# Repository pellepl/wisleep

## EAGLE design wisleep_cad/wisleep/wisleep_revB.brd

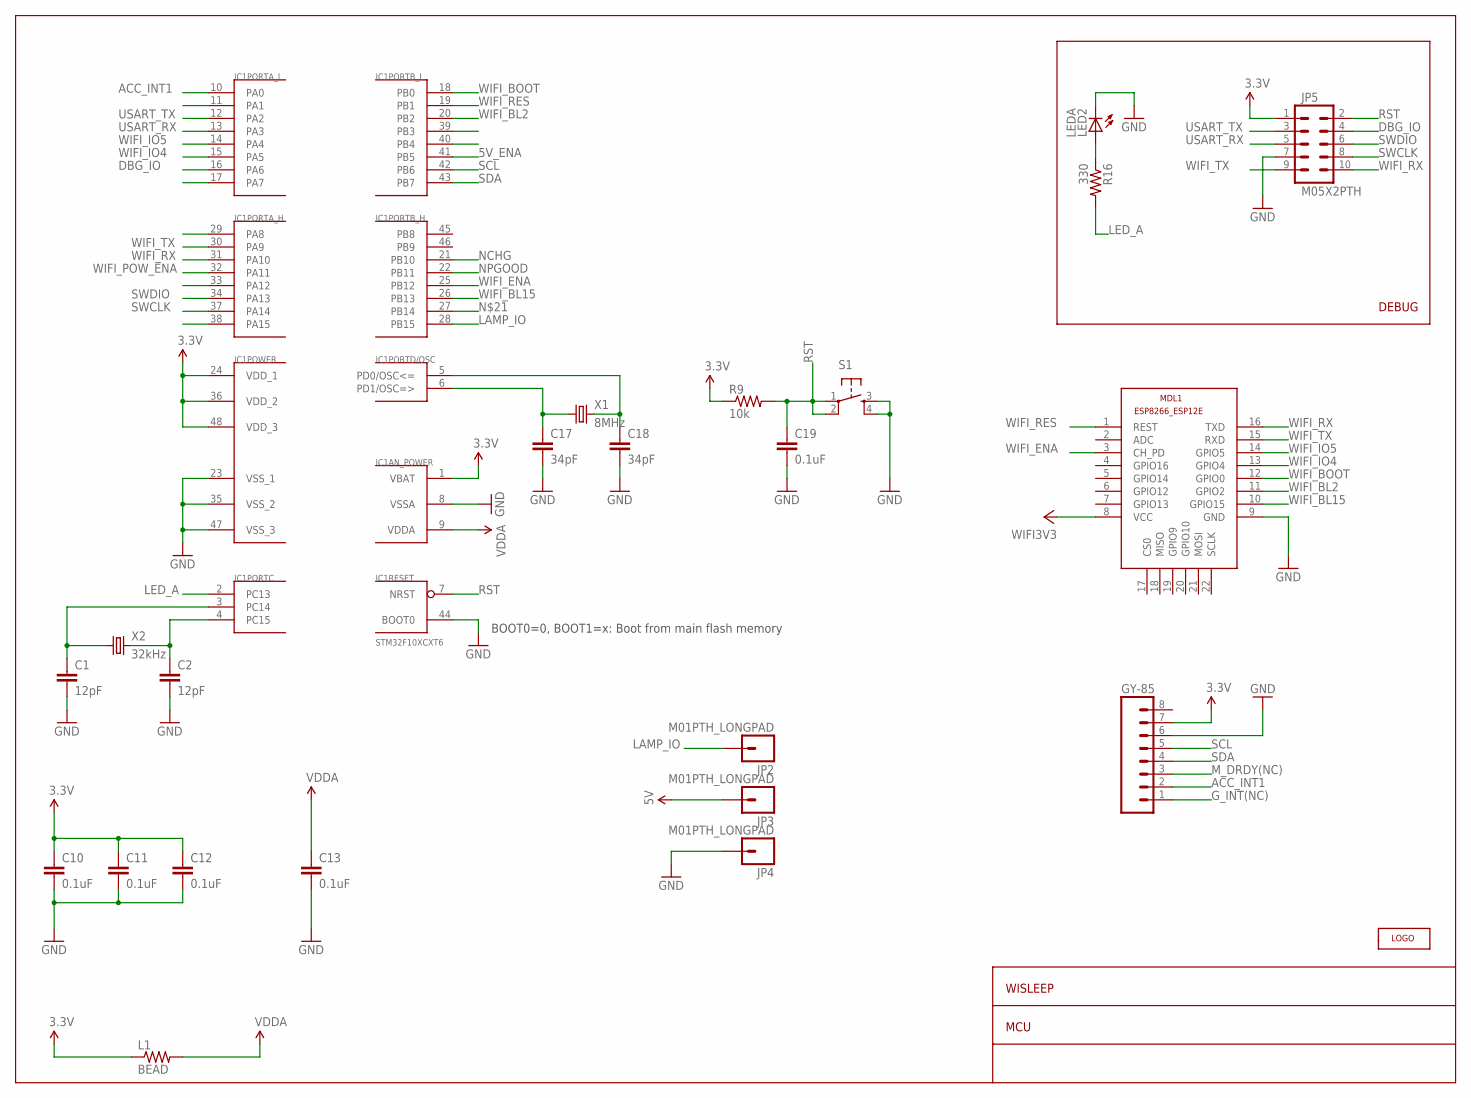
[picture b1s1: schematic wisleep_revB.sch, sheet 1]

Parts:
C1, C2: 12pF; C0402
C10, C11, C12, C13, C19: 0.1uF; C0402
C17, C18: 34pF; C0402
GY-85: M08; 1X08
IC1: STM32F10XCXT6; TQFP48
JP2, JP3, JP4: M01PTH_LONGPAD; 1X01_LONGPAD
JP5: M05X2PTH; AVR_ICSP
L1: BEAD; 0603_GEN
LED2: LEDA; LED-0603
MDL1: ESP8266-12EESP8266-ESP12E; ESP8266-ESP12E
R9: 10k; C0402
R16: 330; C0402
S1: TAC_SWITCHSMD; TACTILE_SWITCH_SMD
U$7: LOGOLOGO; LOGO
X1: 8MHz; CRYSTAL_SMD_5X3.2_7A
X2: 32kHz; CRYSTAL_SMD_2X0.6

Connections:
3.3V: C10.1, C11.1, C12.1, GY-85.7, IC1.1 (VBAT), IC1.24 (VDD_1), IC1.36 (VDD_2), IC1.48 (VDD_3), JP5.1, L1.1, R9.1; also elsewhere on the board
5V: JP3.1; also elsewhere on the board
5V_ENA: IC1.41 (PB5); also elsewhere on the board
ACC_INT1: GY-85.2, IC1.10 (PA0)
DBG_IO: IC1.16 (PA6), JP5.4
GND: C1.2, C2.2, C10.2, C11.2, C12.2, C13.2, C17.2, C18.2, C19.2, GY-85.6, IC1.8 (VSSA), IC1.23 (VSS_1), IC1.35 (VSS_2), IC1.44 (BOOT0), IC1.47 (VSS_3), JP4.1, JP5.7, LED2.C, MDL1.9 (GND), S1.3, S1.4; also elsewhere on the board
G_INT(NC): GY-85.1
LAMP_IO: IC1.28 (PB15), JP2.1
LED_A: IC1.2 (PC13), R16.2
M_DRDY(NC): GY-85.3
unnamed: C1.1, IC1.3 (PC14), X2.P$1 (1)
unnamed: C2.1, IC1.4 (PC15), X2.P$2 (2)
unnamed: LED2.A, R16.1
NCHG: IC1.21 (PB10); also elsewhere on the board
NPGOOD: IC1.22 (PB11); also elsewhere on the board
OSCI: C18.1, IC1.5 (PD0/OSC<=), X1.P$2 (2)
OSCO: C17.1, IC1.6 (PD1/OSC=>), X1.P$1 (1)
PB3: IC1.39 (PB3)
RST: C19.1, IC1.7 (NRST), JP5.2, R9.2, S1.1, S1.2
SCL: GY-85.5, IC1.42 (PB6)
SDA: GY-85.4, IC1.43 (PB7)
SWCLK: IC1.37 (PA14), JP5.8
SWDIO: IC1.34 (PA13), JP5.6
USART_RX: IC1.13 (PA3), JP5.5
USART_TX: IC1.12 (PA2), JP5.3
VCC: MDL1.8 (VCC); also elsewhere on the board
VDDA: C13.1, IC1.9 (VDDA), L1.2
WIFI_BL2: IC1.20 (PB2), MDL1.11 (GPIO2)
WIFI_BL15: IC1.26 (PB13), MDL1.10 (GPIO15)
WIFI_BOOT: IC1.18 (PB0), MDL1.12 (GPIO0)
WIFI_ENA: IC1.25 (PB12), MDL1.3 (CH_PD)
WIFI_IO4: IC1.15 (PA5), MDL1.13 (GPIO4)
WIFI_IO5: IC1.14 (PA4), MDL1.14 (GPIO5)
WIFI_POW_ENA: IC1.32 (PA11); also elsewhere on the board
WIFI_RES: IC1.19 (PB1), MDL1.1 (REST)
WIFI_RX: IC1.31 (PA10), JP5.10, MDL1.16 (TXD)
WIFI_TX: IC1.30 (PA9), JP5.9, MDL1.15 (RXD)

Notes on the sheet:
WISLEEP
MCU
DEBUG
BOOT0=0, BOOT1=x: Boot from main flash memory

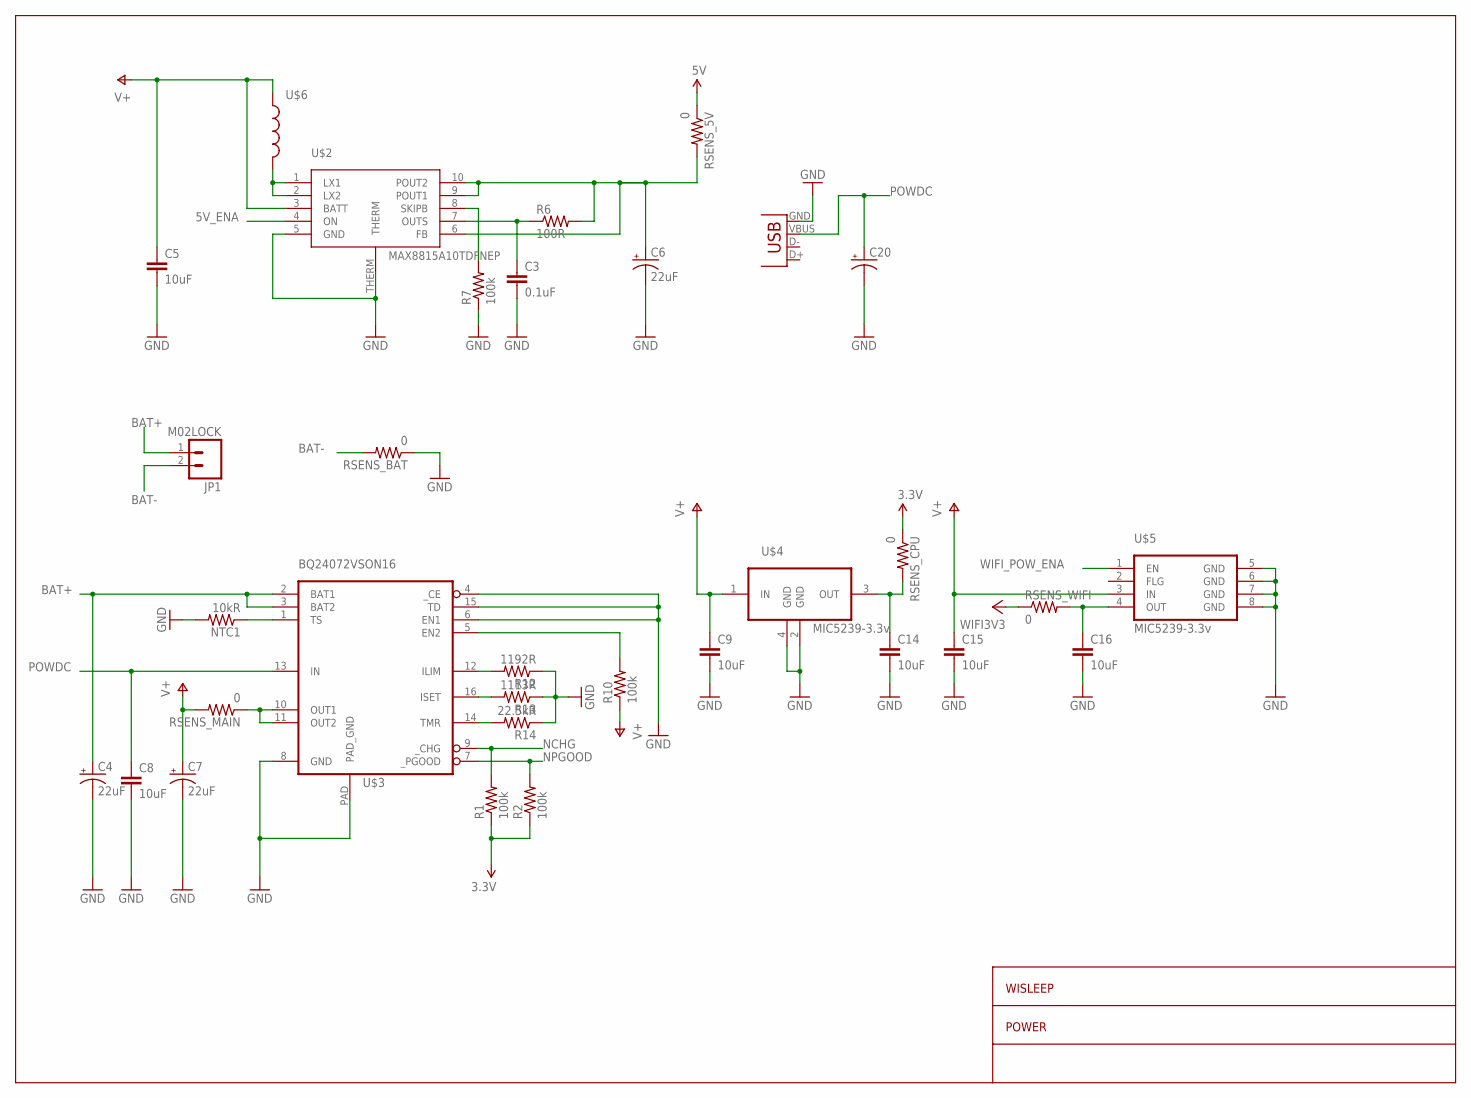
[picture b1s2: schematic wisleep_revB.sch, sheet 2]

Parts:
C3: 0.1uF; C0402
C4, C6, C7: 22uF; EIA3216
C5, C8, C9, C14, C15, C16: 10uF; C0402
C20: CAP_POL6032; EIA6032
JP1: M02LOCK; 1X02_LOCK
NTC1: 10kR; C0402
R1, R2, R7, R10: 100k; C0402
R6: 100R; C0402
R12: 1192R; C0402
R13: 1113R; C0402
R14: 22.5kR; C0402
RSENS_5V: 0; C0402
RSENS_BAT: 0; C0402
RSENS_CPU: 0; C0402
RSENS_MAIN: 0; C0402
RSENS_WIFI: 0; C0402
U$2: MAX8815A10TDFNEP; 10-TDFN-EP
U$3: BQ24072VSON16; VSON16
U$4: MIC5239-3.3v; SOT223
U$5: MIC5239-3.3v; MSOP08
U$6: INDUCTOR3014; INDUCTOR-3014
X3: USB-MINIB

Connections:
3.3V: R1.1, R2.1, RSENS_CPU.1; also elsewhere on the board
5V: RSENS_5V.1; also elsewhere on the board
5V_ENA: U$2.4 (ON); also elsewhere on the board
BAT+: C4.A (+), JP1.1, U$3.2 (BAT1), U$3.3 (BAT2)
BAT-: JP1.2, RSENS_BAT.2
GND: C3.2, C4.C (-), C5.2, C6.C (-), C7.C (-), C8.2, C9.2, C14.2, C15.2, C16.2, C20.P$2 (-), NTC1.2, R7.1, R12.1, R13.1, R14.1, RSENS_BAT.1, U$2.5 (GND), U$2.THERM, U$3.4 (_CE), U$3.6 (EN1), U$3.8 (GND), U$3.15 (TD), U$3.PAD (PAD_GND), U$4.2 (GND), U$4.4 (GND), U$5.5 (GND), U$5.6 (GND), U$5.7 (GND), U$5.8 (GND), X3.GND; also elsewhere on the board
unnamed: C6.A (+), R6.2, RSENS_5V.2, U$2.6 (FB), U$2.9 (POUT1), U$2.10 (POUT2)
unnamed: RSENS_MAIN.1, U$3.10 (OUT1), U$3.11 (OUT2)
unnamed: R14.2, U$3.14 (TMR)
unnamed: NTC1.1, U$3.1 (TS)
unnamed: R10.2, U$3.5 (EN2)
unnamed: R12.2, U$3.12 (ILIM)
unnamed: R13.2, U$3.16 (ISET)
unnamed: C14.1, RSENS_CPU.2, U$4.3 (OUT)
unnamed: C16.1, RSENS_WIFI.2, U$5.4 (OUT)
unnamed: U$2.1 (LX1), U$2.2 (LX2), U$6.P$2 (2)
unnamed: C3.1, R6.1, U$2.7 (OUTS)
unnamed: R7.2, U$2.8 (SKIPB)
NCHG: R1.2, U$3.9 (_CHG); also elsewhere on the board
NPGOOD: R2.2, U$3.7 (_PGOOD); also elsewhere on the board
POWDC: C8.1, C20.P$1 (+), U$3.13 (IN), X3.VBUS
V+: C5.1, C7.A (+), C9.1, C15.1, R10.1, RSENS_MAIN.2, U$2.3 (BATT), U$4.1 (IN), U$5.3 (IN), U$6.P$1 (1)
VCC: RSENS_WIFI.1; also elsewhere on the board
WIFI_POW_ENA: U$5.1 (EN); also elsewhere on the board

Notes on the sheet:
WISLEEP
POWER

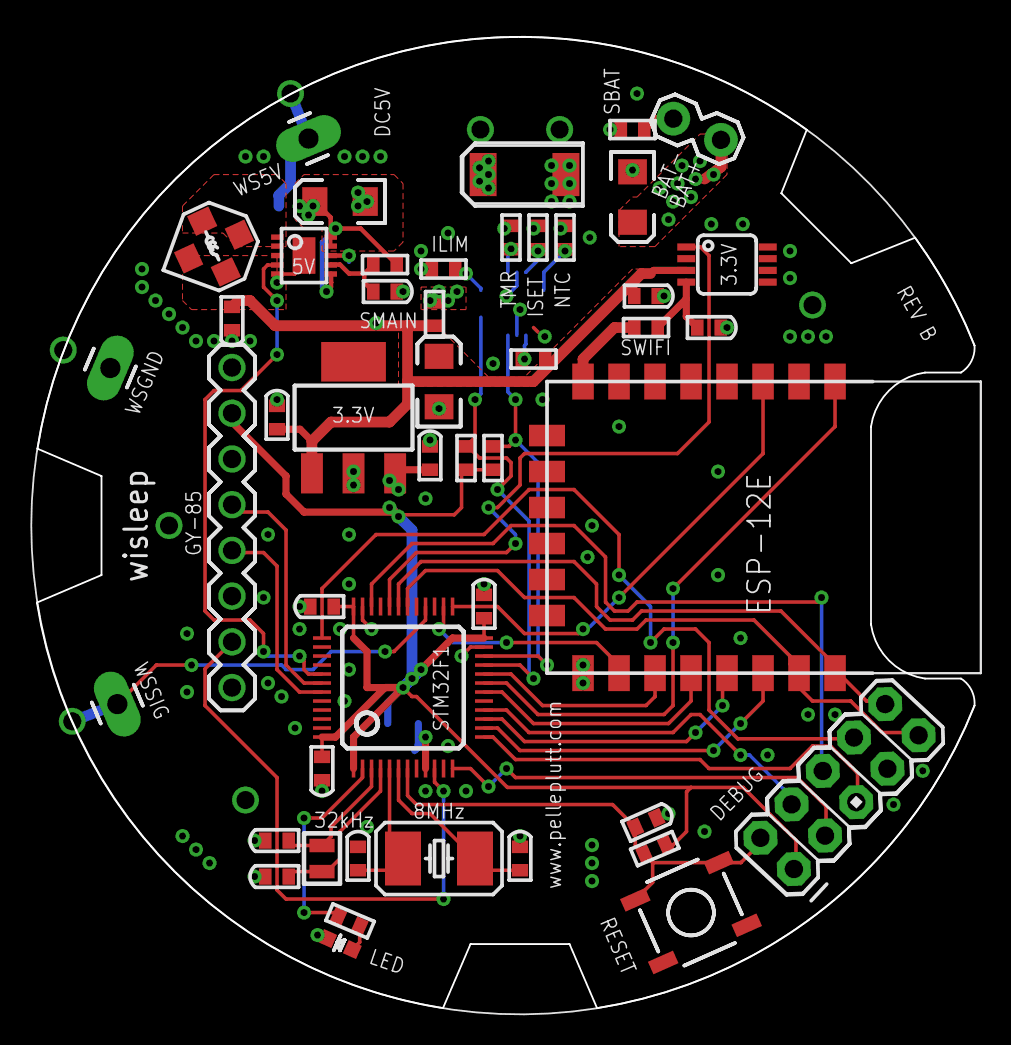
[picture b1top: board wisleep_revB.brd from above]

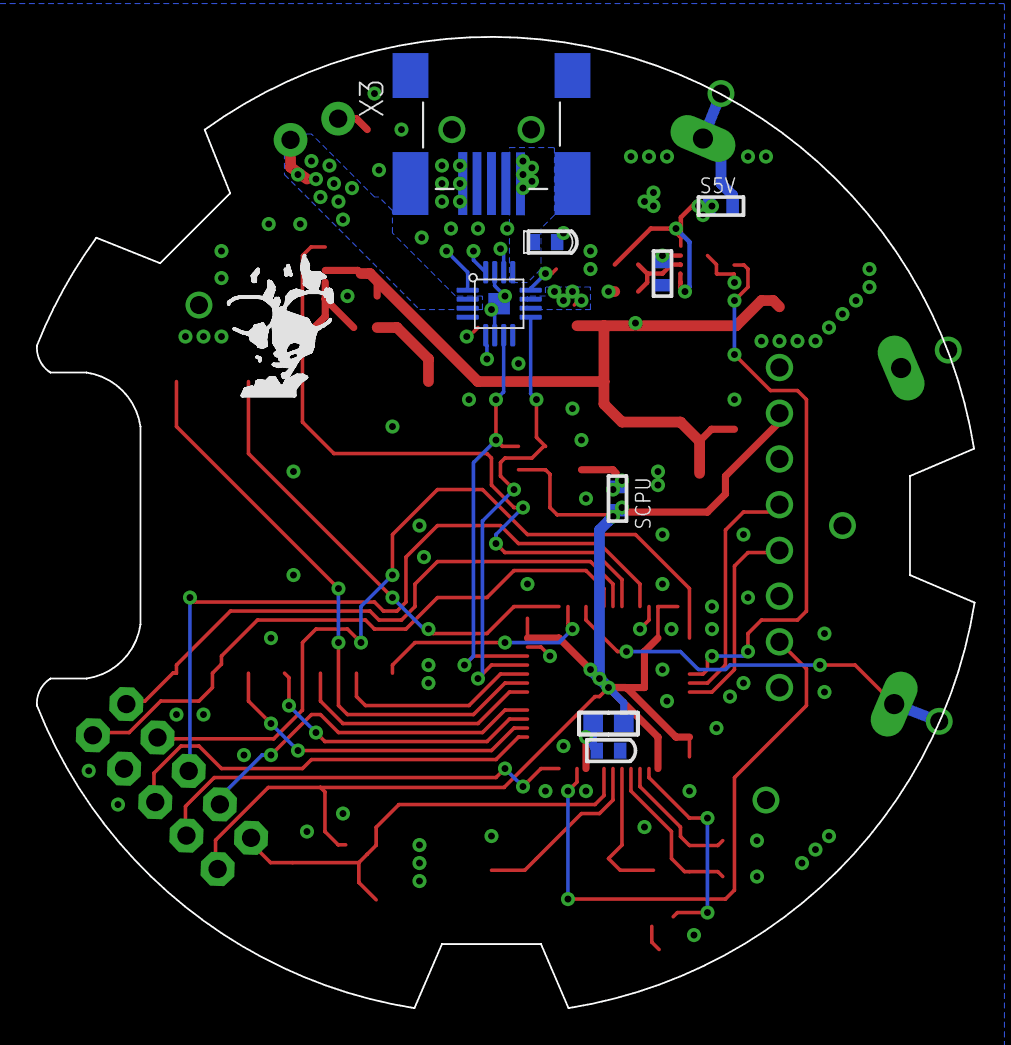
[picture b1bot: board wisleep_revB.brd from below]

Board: 2 copper layers, 52.1 x 54.0 mm, 56 parts (9 on the bottom side), 50 nets.

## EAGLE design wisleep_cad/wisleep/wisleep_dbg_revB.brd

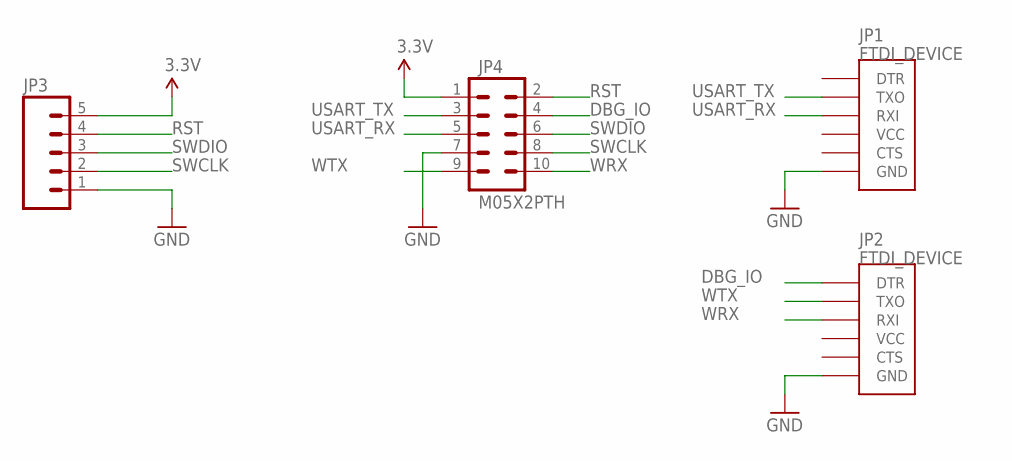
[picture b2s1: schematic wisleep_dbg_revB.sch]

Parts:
JP1, JP2: FTDI_DEVICE; FTDI_DEVICE_SIDE
JP3: M05LOCK; 1X05_LOCK
JP4: M05X2PTH; AVR_ICSP

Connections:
3.3V: JP3.5, JP4.1
DBG_IO: JP2.P$1 (DTR), JP4.4
GND: JP1.P$6 (GND), JP2.P$6 (GND), JP3.1, JP4.7
RST: JP3.4, JP4.2
SWCLK: JP3.2, JP4.8
SWDIO: JP3.3, JP4.6
USART_RX: JP1.P$3 (RXI), JP4.5
USART_TX: JP1.P$2 (TXO), JP4.3
WRX: JP2.P$3 (RXI), JP4.10
WTX: JP2.P$2 (TXO), JP4.9

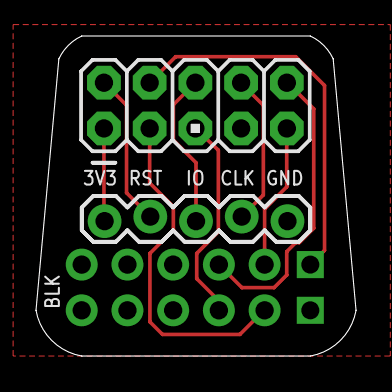
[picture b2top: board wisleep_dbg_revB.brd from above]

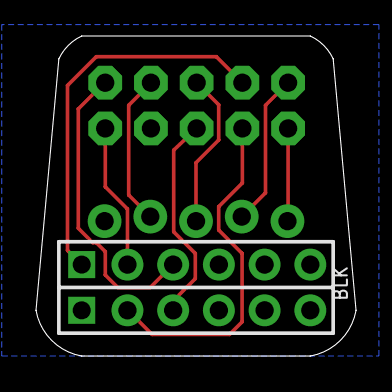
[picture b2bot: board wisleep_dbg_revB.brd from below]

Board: 2 copper layers, 17.8 x 17.8 mm, 4 parts (2 on the bottom side), 10 nets.

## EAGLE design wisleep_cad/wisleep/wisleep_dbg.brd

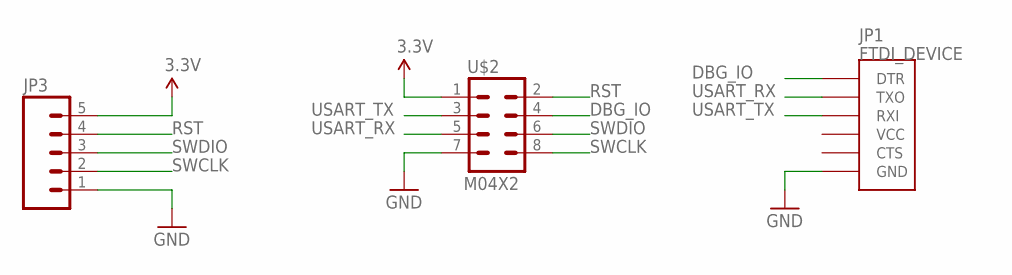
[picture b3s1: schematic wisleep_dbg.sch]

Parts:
JP1: FTDI_DEVICE; FTDI_DEVICE_SIDE
JP3: M05LOCK; 1X05_LOCK
U$2: M04X2; 2X4

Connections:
3.3V: JP3.5, U$2.1
DBG_IO: JP1.P$1 (DTR), U$2.4
GND: JP1.P$6 (GND), JP3.1, U$2.7
RST: JP3.4, U$2.2
SWCLK: JP3.2, U$2.8
SWDIO: JP3.3, U$2.6
USART_RX: JP1.P$2 (TXO), U$2.5
USART_TX: JP1.P$3 (RXI), U$2.3

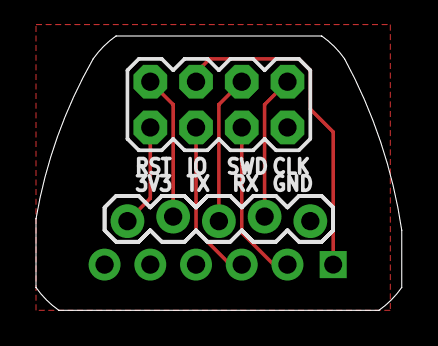
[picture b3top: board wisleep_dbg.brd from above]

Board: 2 copper layers, 20.3 x 15.2 mm, 3 parts (1 on the bottom side), 8 nets.

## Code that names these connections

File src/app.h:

/*
 * app.h
 *
 *  Created on: Jan 2, 2014
 *      Author: petera
 */

#ifndef APP_H_
#define APP_H_

#include "system.h"

#define WIFIDO_VERSION        0x00010100

#define PIN_ACC_INT           PORTA, PIN0
#define PIN_UART_TX           PORTA, PIN2
#define PIN_UART_RX           PORTA, PIN3

#define PIN_WIFI_IO5          PORTA, PIN4
#define PIN_WIFI_IO4          PORTA, PIN5

#define PIN_DEBUG_IO          PORTA, PIN6

#define PIN_WIFI_UART_TX      PORTA, PIN9
#define PIN_WIFI_UART_RX      PORTA, PIN10

#define PIN_POW_WIFI          PORTA, PIN11

#define PIN_WIFI_BOOT         PORTB, PIN0
#define PIN_WIFI_RESET        PORTB, PIN1
#define PIN_WIFI_BL2          PORTB, PIN2

#define PIN_POW_5V            PORTB, PIN3

#define PIN_I2C1_SCL          PORTB, PIN6
#define PIN_I2C1_SDA          PORTB, PIN7

#define PIN_POW_NCHG          PORTB, PIN10
#define PIN_POW_NPGOOD        PORTB, PIN11

#define PIN_WIFI_ENA          PORTB, PIN12
#define PIN_WIFI_BL15         PORTB, PIN13

#define PIN_LAMP_CTRL         PORTB, PIN15

#define PIN_LED               PORTC, PIN13

#define ESP_FLASH_PROGRAMMING_BAUD_RATE 115200

#define APP_PREVENT_SLEEP_IF_LESS_MS    20
#define APP_WDOG_TIMEOUT_S              23
#define APP_HEARTBEAT_MS                20000
#define APP_CLI_POLL_MS                 1000
#define APP_TEMPERATURE_MS              1000*60*60
#define APP_CLI_INACT_SHUTDOWN_S        3
#define APP_KEEP_SENSORS_ALIVE_S        15

#define CLAIM_CLI             0x00
#define CLAIM_SEN             0x01
#define CLAIM_ACC             0x02
#define CLAIM_MAG             0x03
#define CLAIM_GYR             0x04
#define CLAIM_LMP             0x05
#define CLAIM_SWP             0x06

// initializes application
void APP_init(void);
void APP_shutdown(void);
void APP_claim(u8_t resource);
void APP_release(u8_t resource);
void APP_report_activity(bool activity, bool inactivity, bool tap, bool doubletap, bool issleep);
void APP_report_temperature(float temp);
void APP_report_data(
    s16_t ax, s16_t ay, s16_t az,
    s16_t mx, s16_t my, s16_t mz,
    s16_t gx, s16_t gy, s16_t gz);

void WB_init(void);

#endif /* APP_H_ */

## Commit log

2015-12-28 initial: copy from wifido
2015-12-28 fixed up openocd connection
2015-12-28 initial pinmap descr
2015-12-28 making it build
2016-01-01 fixups, hmc5883 driver, ws2812b driver
2016-01-07 name corrections, started adxl345 driver
2016-01-12 more changes, about to modify the ws2812 to 3 bits instead
2016-01-12 ws2812 got rid of green first led
2016-01-17 ws2812 cleanup, adxl345 ifc done
2016-01-19 adxl345 finished, untested
2016-01-26 bwah - too much to describe
2016-01-26 updated sub
2016-01-29 restructure cli
2016-01-31 moved adxl and hmc to generic
2016-01-31 updated generic
2016-01-31 updated makefile, removed duplicates from generic
2016-01-31 upped generic, added dev cli
2016-02-01 upped generic, mod app acc to new cli struct
2016-02-01 wdog
2016-02-01 reordered config, upped gen
2016-02-04 oops + other changes
2016-02-04 upped gen
2016-02-04 moved debug memory to non overlapping shmem
2016-02-04 sleep poc
2016-02-05 sleep, STOP mode
2016-02-06 uart detection poc, rtc stuff, upped gen
2016-02-06 cleanup, uart detect
2016-02-07 rtc fixes, more cleanup
2016-02-07 task loop fixxup
2016-02-08 sensoric input started
2016-02-10 sensor impl, timer fix, minor cli stuff
2016-02-10 wakeup on acc activity, sleep on inactivity
2016-02-10 interval temp reading
2016-02-10 playing around with lamp control
2016-02-11 more ui friendly, lamp improvements
2016-02-11 pinmapped, some cad, taskified things in lamp
2016-02-12 adhere to new formatted printing
2016-02-12 adhere to new formatted longlong printing
2016-02-13 ifdeffed the uart detection, seems to slow things down
2016-02-13 prepare for esp8266 development
2016-02-14 added extra uart
2016-02-14 added an esp8266 terminal example
2016-02-15 turned off trace, saved some flash
2016-02-15 fixed assure tx to correct uart
2016-02-16 simple MAC protocol, incorporated at stm side
2016-02-17 taskified protocol data reception
2016-02-18 renamed protocol symbols to umac
2016-02-18 renamed protocol files to umac
2016-02-18 adhere to new time name
2016-02-20 esp8266 tests
2016-02-24 esp umac impl begun
2016-02-25 some basic stm32/esp8266 comm tests
2016-02-27 new initial params for lamp during dev
2016-02-27 fix umac seqno bug
2016-02-27 update umac cfg to new src
2016-02-27 more esp dev
2016-02-27 redirect stdout via io inst of uart directly
2016-03-02 esp8266, uweb integration
2016-03-03 esp: added spiffs, added more server, uweb upped
2016-03-03 esp server files
2016-03-04 upped subprojects
2016-03-04 upped uweb, adhere to new ifc
2016-03-05 upped uweb
2016-03-05 first page from spiffs served over web
2016-03-14 upped subprojs
2016-03-14 more server func
2016-04-07 upped externals
2016-04-07 fixed an alignment problem with spi driver, more func
2016-04-10 busy handling of server, not finished
2016-04-11 scan test
2016-04-11 busy handling finished, ap scan, upped uweb
2016-04-12 fixed bug when uploading file
2016-04-12 added content for colorpicking
2016-04-12 fixed up bad tagendings
2016-04-12 fixxed up setting of color, fixed up params in server
2016-04-13 js hakking
2016-04-13 speaking html->wifi2esp->uart2stm->lamp
2016-04-13 firefox+chromium, not android
2016-04-13 filled in protocol on both sides
2016-04-14 trying to sync color on page load, wierdnesses
2016-04-14 closer to finding the bug
2016-04-15 renamed a bit
2016-04-15 renamed a bit more
2016-04-15 fixed comm bug, taskified too much
2016-04-15 intensity controllable
2016-04-16 lamp control, on off via intensity
2016-04-16 ntp started
2016-04-17 server socket tmo
2016-04-18 udp from stm->esp->wifi
2016-04-19 udp broadcasting tx/rx
2016-04-19 esp/stm ping capability
2016-04-20 basic udp handling
2016-04-20 reenabled some gensys stuff
2016-04-24 added specs, upped externals
2016-04-26 some more cad
2016-05-11 more cadding
2016-05-11 upped spiffs
2016-05-12 even moar cad
2016-05-18 pinmap changes
2016-05-18 cadding soon to an end
2016-05-19 wisleep cad rev A - 2 fab
2016-05-23 fixed up dc jack holes, resent to fab
2016-05-23 cadded dbg conn
2016-06-26 adhere to new rev A
2016-06-28 cad: dbg board, flipped rx & tx (as always)
2016-06-28 cad: rev B started
    fixed reversed ordering of pins on battery charger
    fixed reversed ordering of pins on inductor
2016-06-30 esp programming - did not work with sw tunnel, do it hw-wise on dbg port
2016-07-04 cad: rev B to fab
2016-07-05 added cli for setting ap and ap scan
2016-07-05 upped ext again

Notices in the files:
parts and their libraries:
SparkFun-Connectors: Licensing: CC v3.0 Share-Alike You are welcome to use this library for commercial purposes.
